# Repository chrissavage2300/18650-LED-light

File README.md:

# 18650-LED-light
This is a high powered LED light powered by a 18650 Battery. 

* Uses Cree J Series Neutral white 3030 LED's.
* LED's Run at 150mA for double the amount of flux. They are connected in a 2P3S format. You can chose to solder one side or the other
* Features mounting holes for transparent 3D printed cover to scatter the light and protect the LED's
* Has Space for 2 18650 Lithium Batteries. I plan on reusing ones Ive salvaged which amount to around 1500mAh to 2000mAh.
* Run time at lowest setting (62mA for 1 string) should be 24 Hours using a 1500mAh Battery. This needs to be tested.
* 10 Hours at the brightest setting. 
* Has a built in USB charger with status LED's. Charge current is 500mA.

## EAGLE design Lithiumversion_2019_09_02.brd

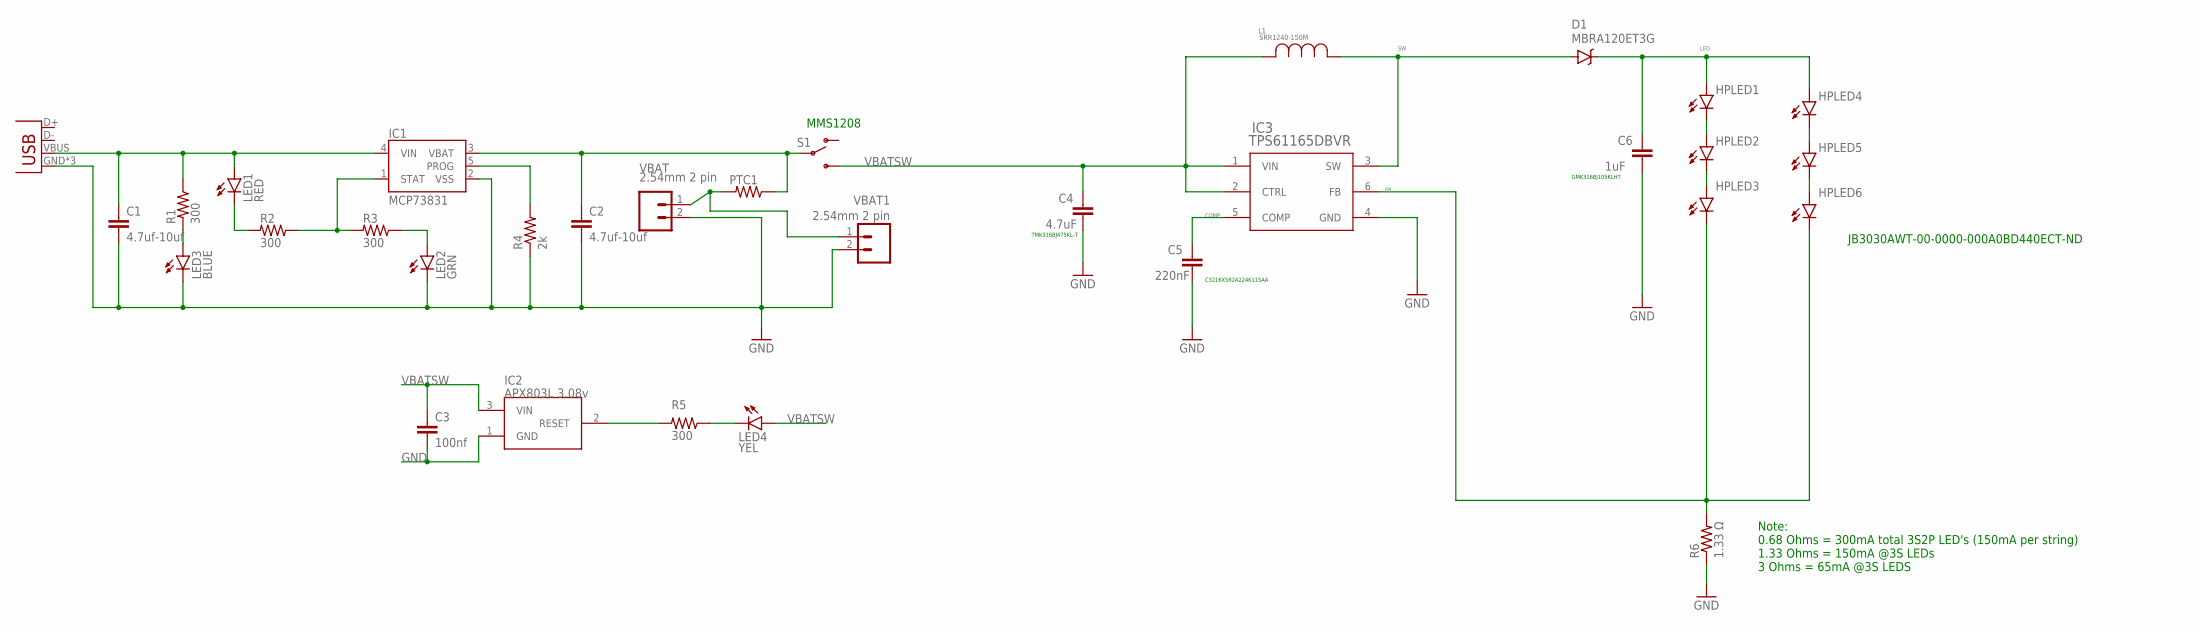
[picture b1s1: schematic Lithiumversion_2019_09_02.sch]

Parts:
C1, C2: 4.7uf-10uf; 1206
C3: 100nf; 1206
C4: 4.7uF; 1206
C5: 220nF; 1206
C6: 1uF; 1206
D1: MBRA120ET3G; SMA-DIODE
HPLED1, HPLED2, HPLED3, HPLED4, HPLED5, HPLED6: CREE_J_3030
IC1: MCP73831; SOT23-5
IC2: APX803L 3.08v; SOT23
IC3: TPS61165DBVR; DBV6
JP3: USB-MICROB
L1: SRR1240-150M; IND_BOURNS_SRR1240
LED1: RED; LED-1206
LED2: GRN; LED-1206
LED3: BLUE; LED-1206
LED4: YEL; LED-1206
PTC1: RESISTOR1206; 1206
R1, R2, R3, R5: 300; 1206
R4: 2k; 1206
R6: 1.33 Ω; 1206
S1: SWITCH-SPDTKIT; SWITCH-SPDT_KIT
VBAT, VBAT1: 2.54mm 2 pin; JST-2-PTH-VERT

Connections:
COMP: C5.2, IC3.5 (COMP)
FB: HPLED3.C, HPLED6.C, IC3.6 (FB), R6.2
GND: C1.2, C2.2, C3.2, C4.1, C5.1, C6.1, IC1.2 (VSS), IC2.1 (GND), IC3.4 (GND), JP3.GND, JP3.MT1 (GND), JP3.MT2 (GND), LED2.C, LED3.C, R4.1, R6.1, VBAT.2, VBAT1.2
LED: C6.2, D1.C, HPLED1.A, HPLED1.A2 (A), HPLED4.A, HPLED4.A2 (A)
unnamed: PTC1.2, VBAT.1, VBAT1.1
unnamed: LED1.C, R2.2
unnamed: IC1.1 (STAT), R2.1, R3.2
unnamed: IC1.5 (PROG), R4.2
unnamed: C1.1, IC1.4 (VIN), JP3.VBUS, LED1.A, R1.1
unnamed: LED2.A, R3.1
unnamed: IC2.2 (RESET), R5.2
unnamed: LED3.A, R1.2
unnamed: LED4.C, R5.1
unnamed: HPLED1.C, HPLED2.A, HPLED2.A2 (A)
unnamed: HPLED2.C, HPLED3.A, HPLED3.A2 (A)
unnamed: HPLED4.C, HPLED5.A, HPLED5.A2 (A)
unnamed: HPLED5.C, HPLED6.A, HPLED6.A2 (A)
SW: D1.A, IC3.3 (SW), L1.1
VBATSW: C3.1, C4.2, IC2.3 (VIN), IC3.1 (VIN), IC3.2 (CTRL), L1.2, LED4.A, S1.3 (S)
VCHARGE: C2.1, IC1.3 (VBAT), PTC1.1, S1.2

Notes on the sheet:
JB3030AWT-00-0000-000A0BD440ECT-ND
GMK316BJ105KLHT
‎TMK316BJ475KL-T‎
‎C3216X5R2A224K115AA‎
Note: 0.68 Ohms = 300mA total 3S2P LED's (150mA per string) 1.33 Ohms = 150mA @3S LEDs 3 Ohms = 65mA @3S LEDS
‎MMS1208‎

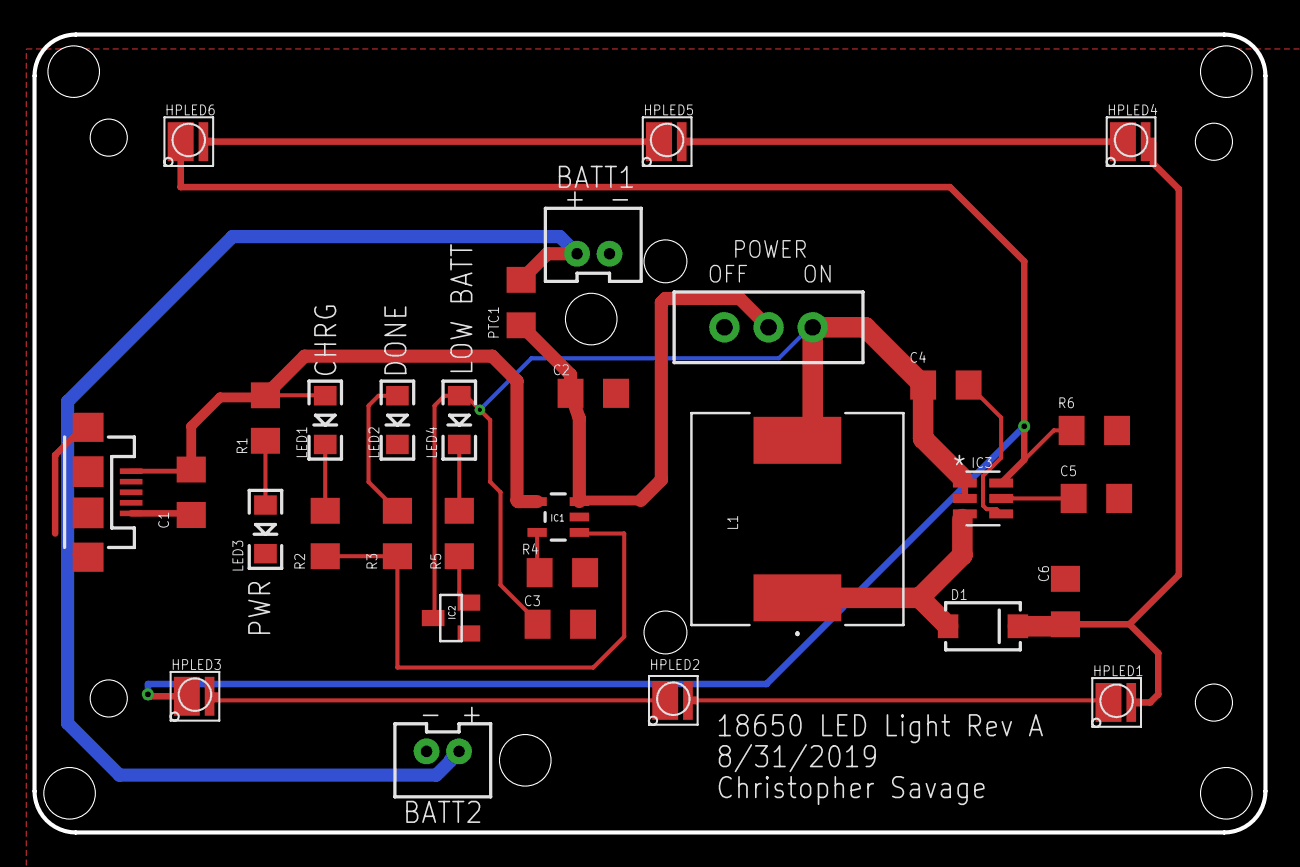
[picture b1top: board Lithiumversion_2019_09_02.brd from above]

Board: 2 copper layers, 75.8 x 49.1 mm, 32 parts (0 on the bottom side), 20 nets.

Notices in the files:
parts and their libraries:
SparkFun-Capacitors: Licensing: Creative Commons ShareAlike 4.0 International - https://creativecommons.org/licenses/by-sa/4.0
